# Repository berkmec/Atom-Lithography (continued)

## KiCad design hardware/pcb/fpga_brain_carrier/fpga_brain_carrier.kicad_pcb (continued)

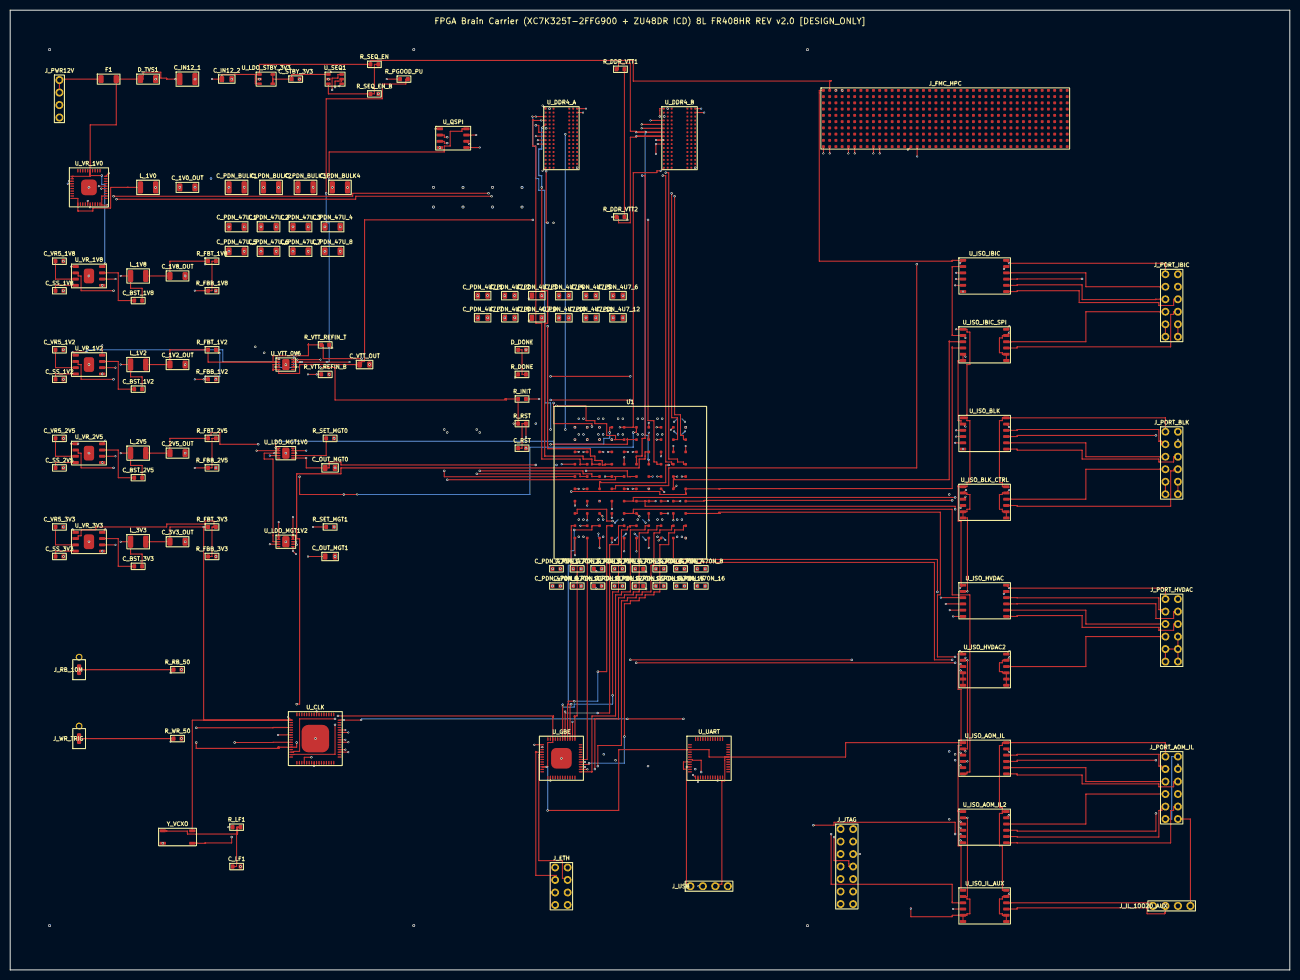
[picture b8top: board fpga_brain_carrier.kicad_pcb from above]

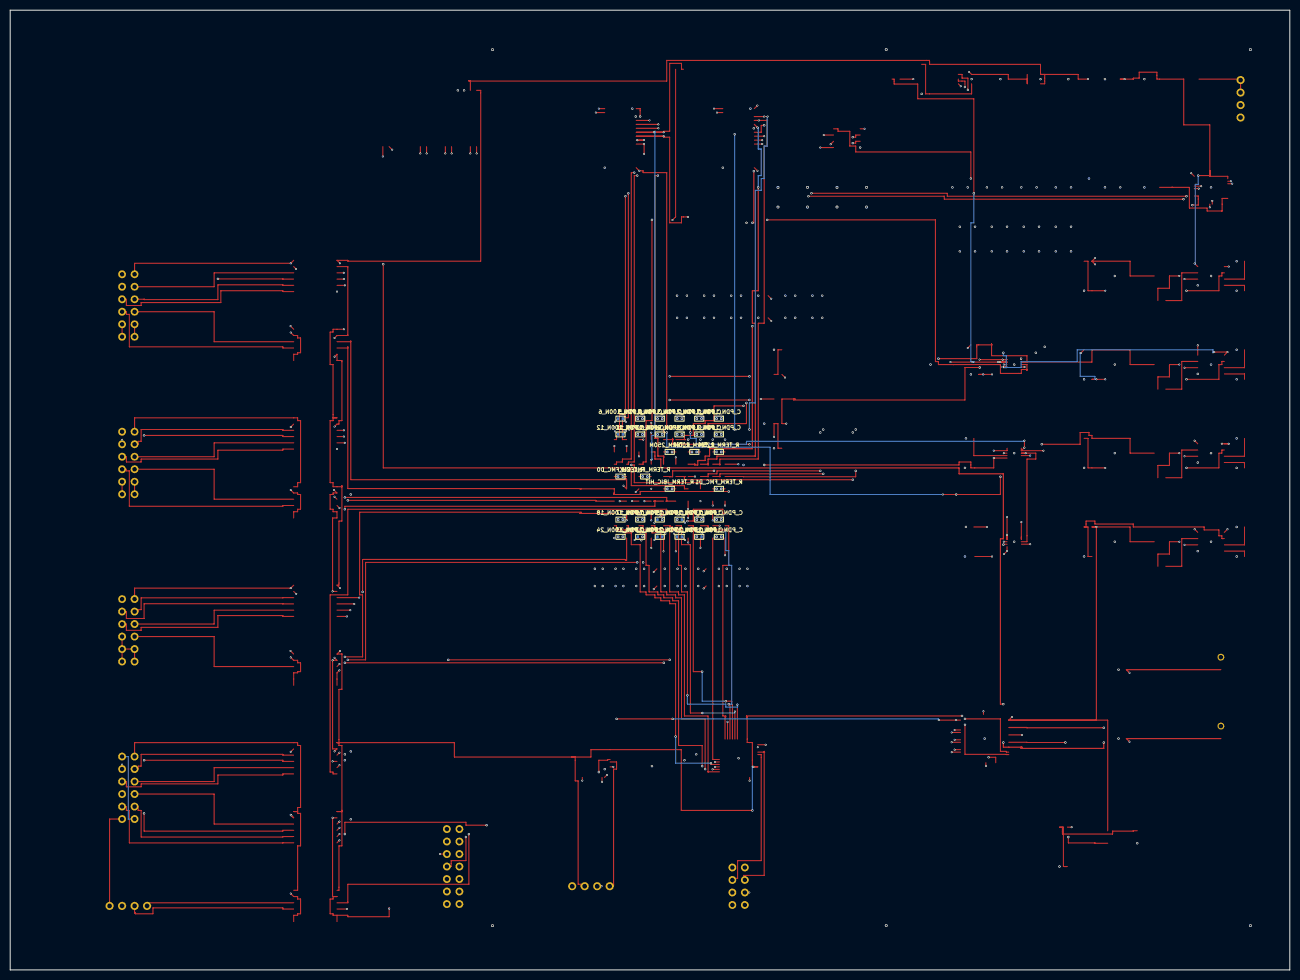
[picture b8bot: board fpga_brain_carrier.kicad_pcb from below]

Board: 8 copper layers, 260.0 x 195.0 mm, 166 parts (31 on the bottom side), 171 nets.
